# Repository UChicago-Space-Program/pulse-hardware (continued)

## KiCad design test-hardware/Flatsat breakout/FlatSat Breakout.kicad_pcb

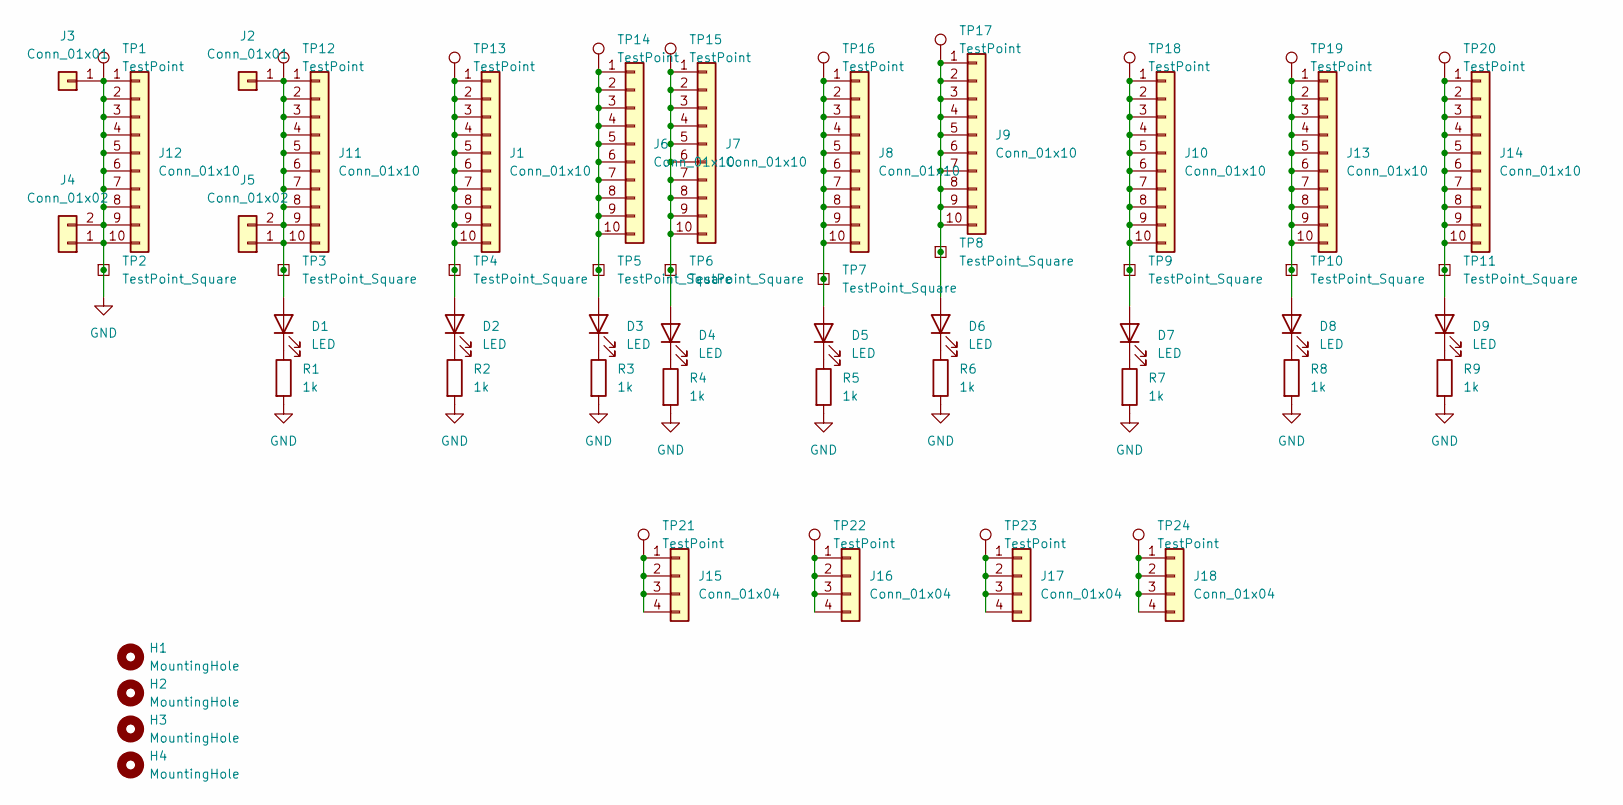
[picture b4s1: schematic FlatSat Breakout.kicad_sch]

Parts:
D1, D2, D3, D4, D5, D6, D7, D8, D9: LED; LED_0603_1608Metric
H1, H2, H3, H4: MountingHole; MountingHole_3.2mm_M3
J1, J6, J7, J8, J9, J10, J11, J12, J13, J14: Conn_01x10; PinHeader_1x10_P2.54mm_Vertical
J2, J3: Conn_01x01; Banana_Jack_1Pin
J4, J5: Conn_01x02; TerminalBlock_4Ucon_1x02_P3.50mm_Horizontal
J15, J16, J17, J18: Conn_01x04; PinHeader_1x04_P2.54mm_Vertical
R1, R2, R3, R4, R5, R6, R7, R8, R9: 1k; R_0603_1608Metric
TP1, TP12, TP13, TP14, TP15, TP16, TP17, TP18, TP19, TP20, TP21, TP22, TP23, TP24: TestPoint; TestPoint_Keystone_5000-5004_Miniature
TP2, TP3, TP4, TP5, TP6, TP7, TP8, TP9, TP10, TP11: TestPoint_Square; TestPoint_Pad_2.0x2.0mm

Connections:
GND: J3.1 (Pin_1_1), J4.1, J4.2, J12.1, J12.2, J12.3, J12.4, J12.5, J12.6, J12.7, J12.8, J12.9, J12.10, R1.2, R2.2, R3.2, R4.2, R5.2, R6.2, R7.2, R8.2, R9.2, TP1.1 (1_1), TP2.1 (1_1)
unnamed: D1.2 (A), J2.1 (Pin_1_1), J5.1, J5.2, J11.1, J11.2, J11.3, J11.4, J11.5, J11.6, J11.7, J11.8, J11.9, J11.10, TP3.1 (1_1), TP12.1 (1_1)
unnamed: D1.1 (K), R1.1
unnamed: D2.2 (A), J1.1, J1.2, J1.3, J1.4, J1.5, J1.6, J1.7, J1.8, J1.9, J1.10, TP4.1 (1_1), TP13.1 (1_1)
unnamed: D2.1 (K), R2.1
unnamed: D3.2 (A), J6.1, J6.2, J6.3, J6.4, J6.5, J6.6, J6.7, J6.8, J6.9, J6.10, TP5.1 (1_1), TP14.1 (1_1)
unnamed: D3.1 (K), R3.1
unnamed: D4.2 (A), J7.1, J7.2, J7.3, J7.4, J7.5, J7.6, J7.7, J7.8, J7.9, J7.10, TP6.1 (1_1), TP15.1 (1_1)
unnamed: D4.1 (K), R4.1
unnamed: D5.2 (A), J8.1, J8.2, J8.3, J8.4, J8.5, J8.6, J8.7, J8.8, J8.9, J8.10, TP7.1 (1_1), TP16.1 (1_1)
unnamed: D5.1 (K), R5.1
unnamed: D6.2 (A), J9.1, J9.2, J9.3, J9.4, J9.5, J9.6, J9.7, J9.8, J9.9, J9.10, TP8.1 (1_1), TP17.1 (1_1)
unnamed: D6.1 (K), R6.1
unnamed: D7.2 (A), J10.1, J10.2, J10.3, J10.4, J10.5, J10.6, J10.7, J10.8, J10.9, J10.10, TP9.1 (1_1), TP18.1 (1_1)
unnamed: D7.1 (K), R7.1
unnamed: D8.2 (A), J13.1, J13.2, J13.3, J13.4, J13.5, J13.6, J13.7, J13.8, J13.9, J13.10, TP10.1 (1_1), TP19.1 (1_1)
unnamed: D8.1 (K), R8.1
unnamed: D9.2 (A), J14.1, J14.2, J14.3, J14.4, J14.5, J14.6, J14.7, J14.8, J14.9, J14.10, TP11.1 (1_1), TP20.1 (1_1)
unnamed: D9.1 (K), R9.1
unnamed: J15.1, J15.2, J15.3, J15.4, TP21.1 (1_1)
unnamed: J16.1, J16.2, J16.3, J16.4, TP22.1 (1_1)
unnamed: J17.1, J17.2, J17.3, J17.4, TP23.1 (1_1)
unnamed: J18.1, J18.2, J18.3, J18.4, TP24.1 (1_1)

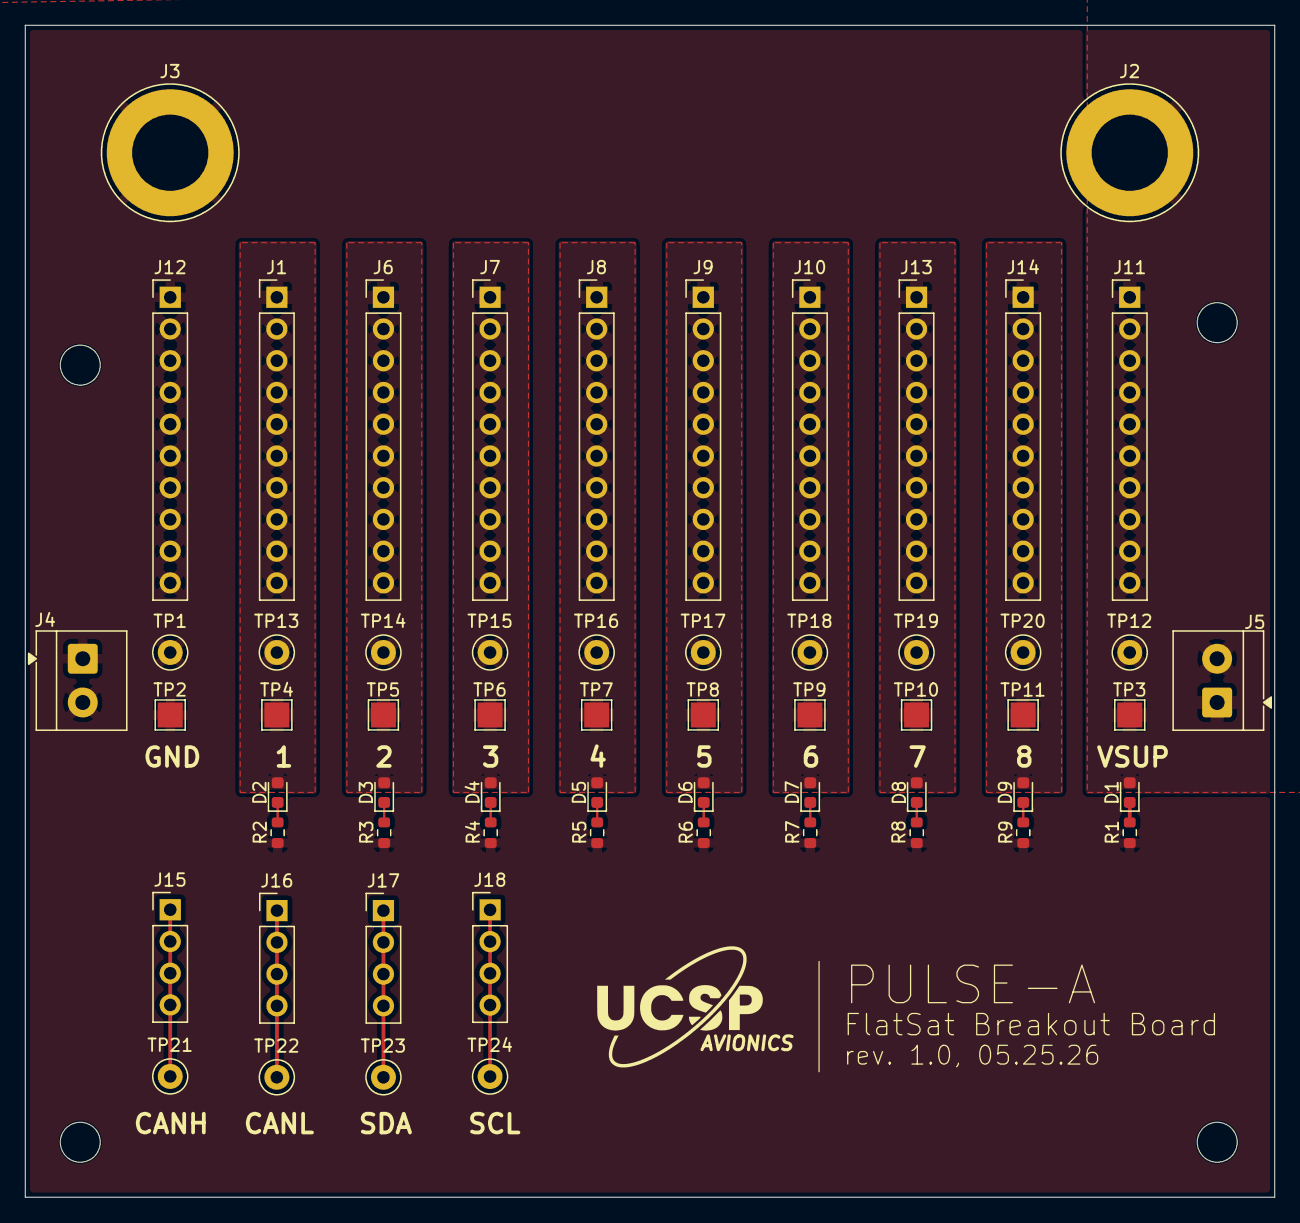
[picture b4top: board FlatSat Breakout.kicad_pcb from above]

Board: 2 copper layers, 100.0 x 93.8 mm, 64 parts (0 on the bottom side), 23 nets.

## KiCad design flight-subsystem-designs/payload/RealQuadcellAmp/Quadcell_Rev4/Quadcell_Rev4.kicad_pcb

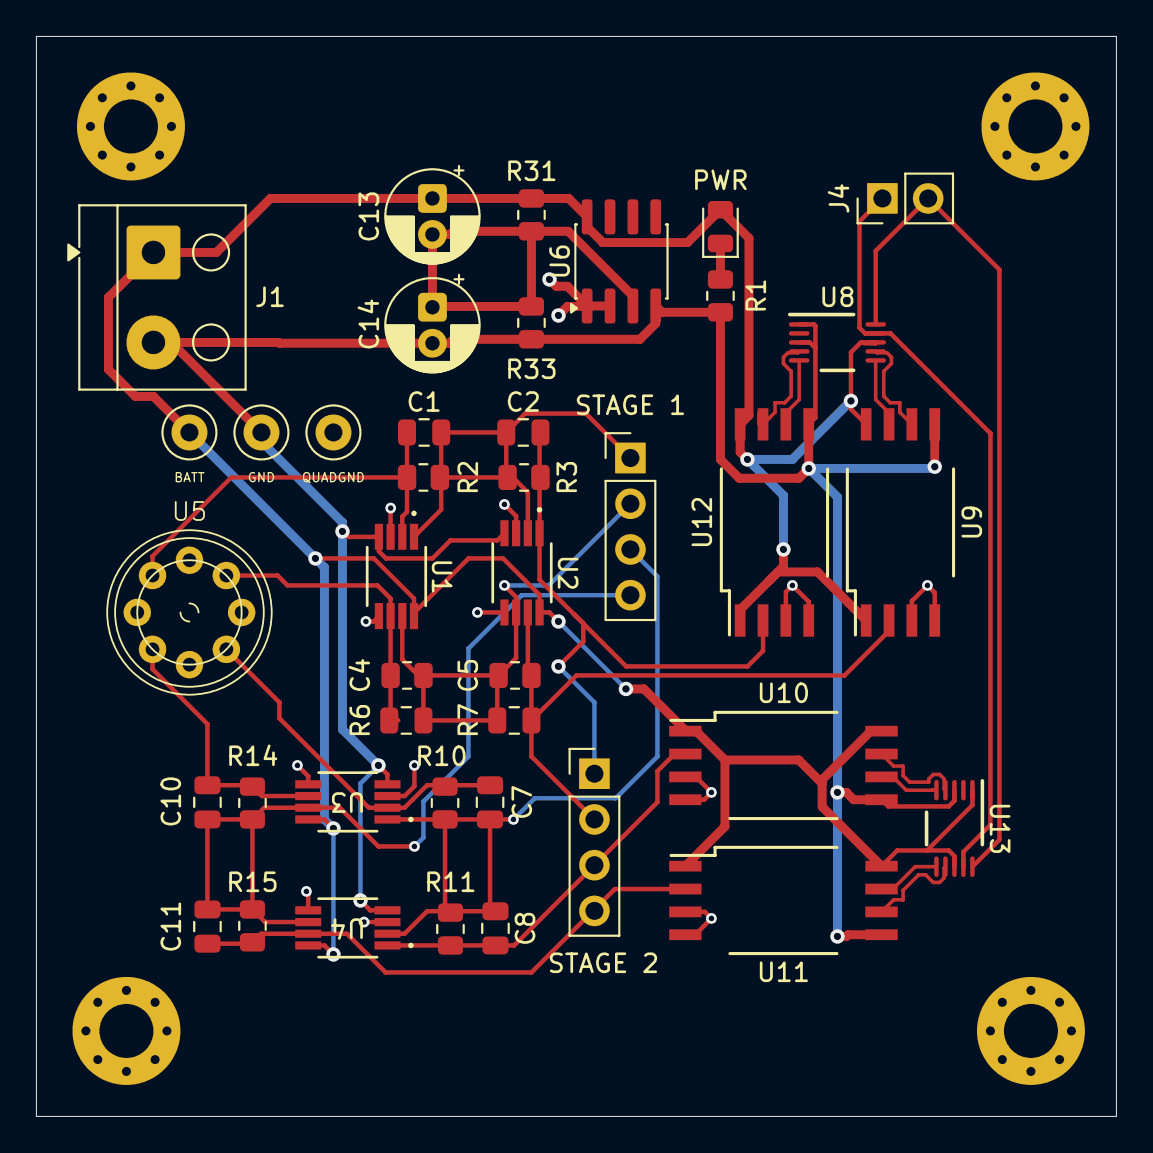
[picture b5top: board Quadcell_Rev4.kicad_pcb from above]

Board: 2 copper layers, 60.0 x 60.0 mm, 45 parts (0 on the bottom side), 27 nets.

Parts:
BATT: TestPoint; TestPoint_Loop_D2.50mm_Drill1.0mm
C1, C4, C7, C10: 5 pf; C_0805_2012Metric
C2, C5, C8, C11: 3 pf; C_0805_2012Metric
C13, C14: 220µF; CP_Radial_D5.0mm_P2.00mm
GND: TestPoint; TestPoint_Loop_D2.50mm_Drill1.0mm
H1, H2, H3, H4: MountingHole_Pad; MountingHole_3mm_Pad_Via
J1: Screw_Terminal_01x02; Altech_AK100_1x02_P5.00mm
J4: Conn_01x02_Pin; PinHeader_1x02_P2.54mm_Vertical
PWR: LED; D_0805_2012Metric
QUADGND: TestPoint; TestPoint_Loop_D2.50mm_Drill1.0mm
R1: 150; R_0805_2012Metric
R2, R6, R10, R14: 1 MΩ; R_0805_2012Metric
R3, R7, R11, R15: 15 MΩ; R_0805_2012Metric
R31, R33: 4.7k; R_0805_2012Metric
STAGE 1, STAGE 2: Conn_01x04_Pin; PinHeader_1x04_P2.54mm_Vertical
U1, U2, U3, U4: OPA2192IDR; OPA2192
U5: InGaAS-Q1000
U6: LM2904; SOIC-8_3.9x4.9mm_P1.27mm
U8, U13: ADS1115IDGST; ADS1115
U9, U10, U11, U12: AMC1301DWVR; AMC1301

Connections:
/digital_conversion/ADC1_N: U8.5 (AIN1), U12.6 (VOUTN)
/digital_conversion/ADC1_P: U8.4 (AIN0), U12.7 (VOUTP)
/digital_conversion/ADC2_N: U8.7 (AIN3), U9.6 (VOUTN)
/digital_conversion/ADC2_P: U8.6 (AIN2), U9.7 (VOUTP)
/digital_conversion/ADC3_N: U10.6 (VOUTN), U13.5 (AIN1)
/digital_conversion/ADC3_P: U10.7 (VOUTP), U13.4 (AIN0)
/digital_conversion/ADC4_N: U11.6 (VOUTN), U13.7 (AIN3)
/digital_conversion/ADC4_P: U11.7 (VOUTP), U13.6 (AIN2)
GND: C14.2, GND.1 (1_1), J1.2, R1.2, R33.2, U1.4 (V-), U2.4 (V-), U3.4 (V-), U4.4 (V-), U6.4 (V-), U8.1 (ADDR), U8.3 (GND), U9.5 (GND2), U10.5 (GND2), U11.5 (GND2), U12.5 (GND2), U13.3 (GND)
I2C_SCL: J4.2, U8.10 (SCL), U13.10 (SCL)
I2C_SDA: J4.1, U8.9 (SDA), U13.9 (SDA)
IN1: C1.1, R2.1, U1.2 (IN-), U5.1 (ANODE_1)
IN2: C4.1, R6.2, U1.6 (IN-), U5.2 (ANODE_2)
IN3: C7.1, R10.2, U3.2 (IN-), U5.3 (ANODE_3)
IN4: C10.1, R14.1, U3.6 (IN-), U5.4 (ANODE_4)
unnamed: PWR.1 (K), R1.1
unnamed: C13.2, C14.1, R31.2, R33.1, U6.3 (+)
QUAD_GND: H1.1 (1_1), H2.1 (1_1), H3.1 (1_1), H4.1 (1_1), QUADGND.1 (1_1), U1.3 (IN+), U1.5 (IN+), U2.3 (IN+), U2.5 (IN+), U3.3 (IN+), U3.5 (IN+), U4.3 (IN+), U4.5 (IN+), U5.0 (CAT), U6.1, U6.2 (-), U9.3 (VINN), U9.4 (GND1), U10.3 (VINN), U10.4 (GND1), U11.3 (VINN), U11.4 (GND1), U12.3 (VINN), U12.4 (GND1)
STAGE1_OUT1: C1.2, C2.1, R2.2, R3.1, STAGE 1.1, U1.1 (OUT), U2.2 (IN-)
STAGE1_OUT2: C4.2, C5.1, R6.1, R7.2, STAGE 1.2, U1.7 (OUT), U2.6 (IN-)
STAGE1_OUT3: C7.2, C8.1, R10.1, R11.2, STAGE 1.3, U3.1 (OUT), U4.2 (IN-)
STAGE1_OUT4: C10.2, C11.1, R14.2, R15.1, STAGE 1.4, U3.7 (OUT), U4.6 (IN-)
STAGE2_OUT1: C2.2, R3.2, STAGE 2.1, U2.1 (OUT), U12.2 (VINP)
STAGE2_OUT2: C5.2, R7.1, STAGE 2.2, U2.7 (OUT), U9.2 (VINP)
STAGE2_OUT3: C8.2, R11.1, STAGE 2.3, U4.1 (OUT), U10.2 (VINP)
STAGE2_OUT4: C11.2, R15.2, STAGE 2.4, U4.7 (OUT), U11.2 (VINP)
VCC: BATT.1 (1_1), C13.1, J1.1, PWR.2 (A), R31.1, U1.8 (V+), U2.8 (V+), U3.8 (V+), U4.8 (V+), U6.8 (V+), U8.8 (VDD), U9.1 (VDD1), U9.8 (VDD2), U10.1 (VDD1), U10.8 (VDD2), U11.1 (VDD1), U11.8 (VDD2), U12.1 (VDD1), U12.8 (VDD2), U13.1 (ADDR), U13.8 (VDD)

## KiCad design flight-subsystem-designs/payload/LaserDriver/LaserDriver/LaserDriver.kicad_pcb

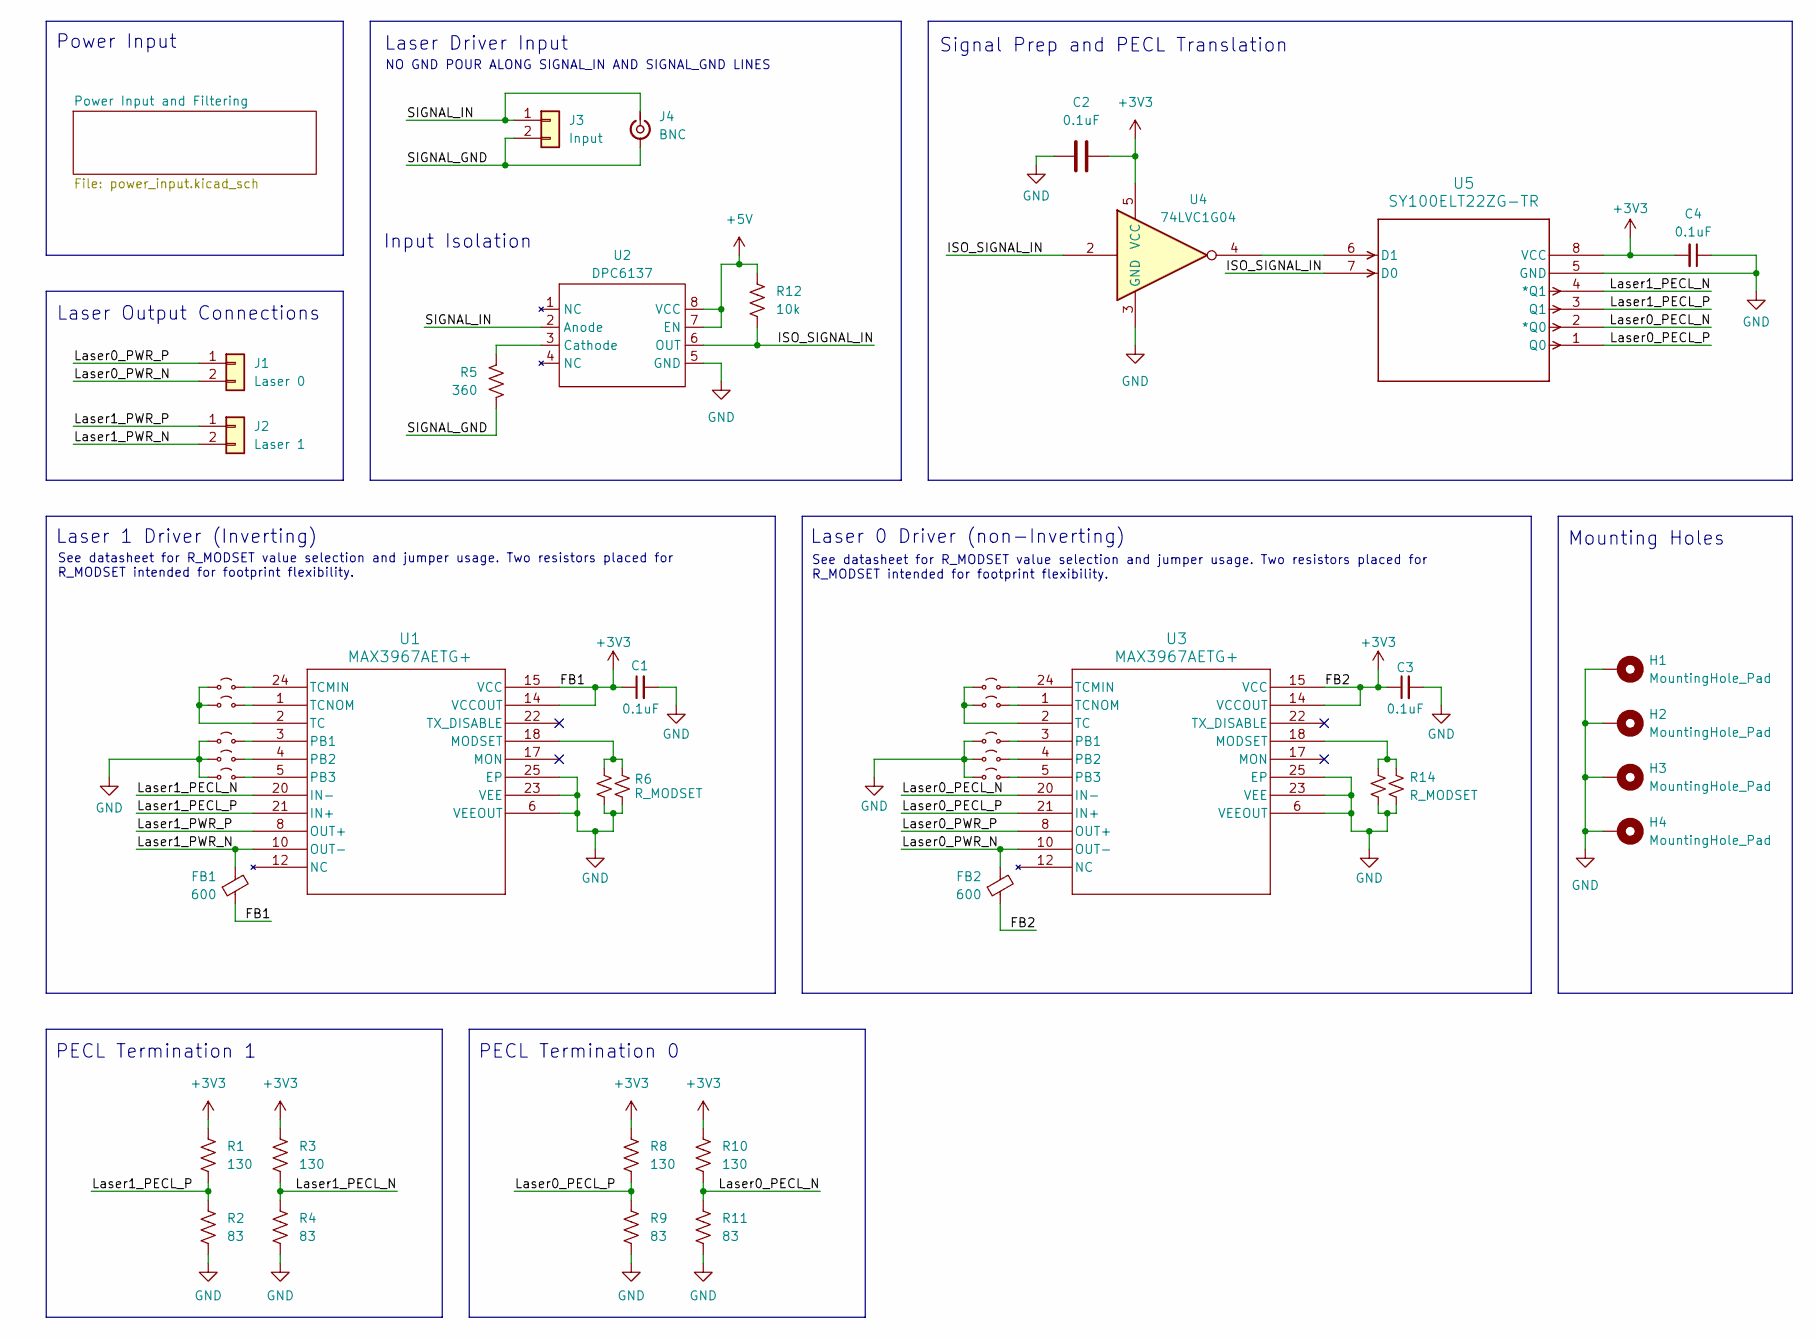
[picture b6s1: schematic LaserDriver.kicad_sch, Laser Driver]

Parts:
C1, C2, C3, C4: 0.1uF; C_0805_2012Metric_Pad1.18x1.45mm_HandSolder
FB1, FB2: 600; L_0805_2012Metric_Pad1.05x1.20mm_HandSolder; DigiKeyPN 445-MPZ2012S601AT000CT-ND
H1, H2, H3, H4: MountingHole_Pad; MountingHole_6.5mm_Pad
J1: Laser 0; PinHeader_1x02_P2.54mm_Vertical
J2: Laser 1; PinHeader_1x02_P2.54mm_Vertical
J3: Input; PinHeader_1x02_P2.54mm_Vertical
J4: BNC; BNC_TEConnectivity_1478204_Vertical
JP1, JP2, JP3, JP4, JP5, JP6, JP7, JP8, JP9, JP10: Jumper_2_Small_Open; SolderJumper-2_P1.3mm_Open_TrianglePad1.0x1.5mm
R1, R3, R8, R10: 130; R_0805_2012Metric_Pad1.20x1.40mm_HandSolder
R2, R4, R9, R11: 83; R_0805_2012Metric_Pad1.20x1.40mm_HandSolder
R5: 360; R_0805_2012Metric
R6, R14: R_MODSET; R_0805_2012Metric_Pad1.20x1.40mm_HandSolder
R7, R13: R_MODSET; R_Axial_DIN0204_L3.6mm_D1.6mm_P7.62mm_Horizontal
R12: 10k; R_0805_2012Metric
U1, U3: MAX3967AETG+; 21-0139_T2444&plus_4_MXM
U2: DPC6137; DIP-8_W10.16mm_LongPads; DigiKey 31-DPC6137W-TU-ND
U4: 74LVC1G04; SOT-23-5_HandSoldering; DigiKeyPN 296-11599-1-ND
U5: SY100ELT22ZG-TR; SOIC-8_M_MCH

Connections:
+3V3: C1.1, C2.2, C3.1, C4.2, FB1.1, FB2.1, R1.1, R3.1, R8.1, R10.1, U1.13 (VCCOUT), U1.14 (VCCOUT), U1.15 (VCC), U1.19 (VCC), U3.13 (VCCOUT), U3.14 (VCCOUT), U3.15 (VCC), U3.19 (VCC), U4.5 (VCC), U5.8 (VCC); also elsewhere on the board
+5V: R12.2, U2.7 (EN), U2.8 (VCC); also elsewhere on the board
/ISO_SIGNAL_IN: R12.1, U2.6 (OUT), U4.2, U5.7 (D0)
/Laser0_PECL_N: R10.2, R11.1, U3.20 (IN-), U5.2 (*Q0)
/Laser0_PECL_P: R8.2, R9.1, U3.21 (IN+), U5.1 (Q0)
/Laser0_PWR_N: FB2.2, J1.2, U3.10 (OUT-), U3.11 (OUT-)
/Laser0_PWR_P: J1.1, U3.8 (OUT+), U3.9 (OUT+)
/Laser1_PECL_N: R3.2, R4.1, U1.20 (IN-), U5.4 (*Q1)
/Laser1_PECL_P: R1.2, R2.1, U1.21 (IN+), U5.3 (Q1)
/Laser1_PWR_N: FB1.2, J2.2, U1.10 (OUT-), U1.11 (OUT-)
/Laser1_PWR_P: J2.1, U1.8 (OUT+), U1.9 (OUT+)
/SIGNAL_GND: J3.2, J4.2 (Ext), R5.1
/SIGNAL_IN: J3.1, J4.1 (In), U2.2 (Anode)
GND: C1.2, C2.1, C3.2, C4.1, H1.1 (1_1), H2.1 (1_1), H3.1 (1_1), H4.1 (1_1), JP3.1 (A), JP4.1 (A), JP5.1 (A), JP8.1 (A), JP9.1 (A), JP10.1 (A), R2.2, R4.2, R6.2, R7.2, R9.2, R11.2, R13.1, R14.1, U1.6 (VEEOUT), U1.7 (VEEOUT), U1.23 (VEE), U1.25 (EP), U2.5 (GND), U3.6 (VEEOUT), U3.7 (VEEOUT), U3.23 (VEE), U3.25 (EP), U4.3 (GND), U5.5 (GND); also elsewhere on the board
unnamed: JP1.1 (A), JP2.1 (A), U1.2 (TC)
unnamed: JP1.2 (B), U1.24 (TCMIN)
unnamed: JP2.2 (B), U1.1 (TCNOM)
unnamed: JP3.2 (B), U1.3 (PB1)
unnamed: JP4.2 (B), U1.4 (PB2)
unnamed: JP5.2 (B), U1.5 (PB3)
unnamed: JP6.1 (A), JP7.1 (A), U3.2 (TC)
unnamed: JP6.2 (B), U3.24 (TCMIN)
unnamed: JP7.2 (B), U3.1 (TCNOM)
unnamed: JP8.2 (B), U3.3 (PB1)
unnamed: JP9.2 (B), U3.4 (PB2)
unnamed: JP10.2 (B), U3.5 (PB3)
unnamed: R6.1, R7.1, U1.18 (MODSET)
unnamed: R5.2, U2.3 (Cathode)
unnamed: R13.2, R14.2, U3.18 (MODSET)
unnamed: U4.4, U5.6 (D1)

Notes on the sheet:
Laser Output Connections
Mounting Holes
NO GND POUR ALONG SIGNAL_IN AND SIGNAL_GND LINES
See datasheet for R_MODSET value selection and jumper usage. Two resistors placed for R_MODSET intended for footprint flexibility.
Laser 1 Driver (Inverting)
Laser Driver Input
PECL Termination 1
PECL Termination 0
Input Isolation
Signal Prep and PECL Translation
Laser 0 Driver (non-Inverting)
Power Input

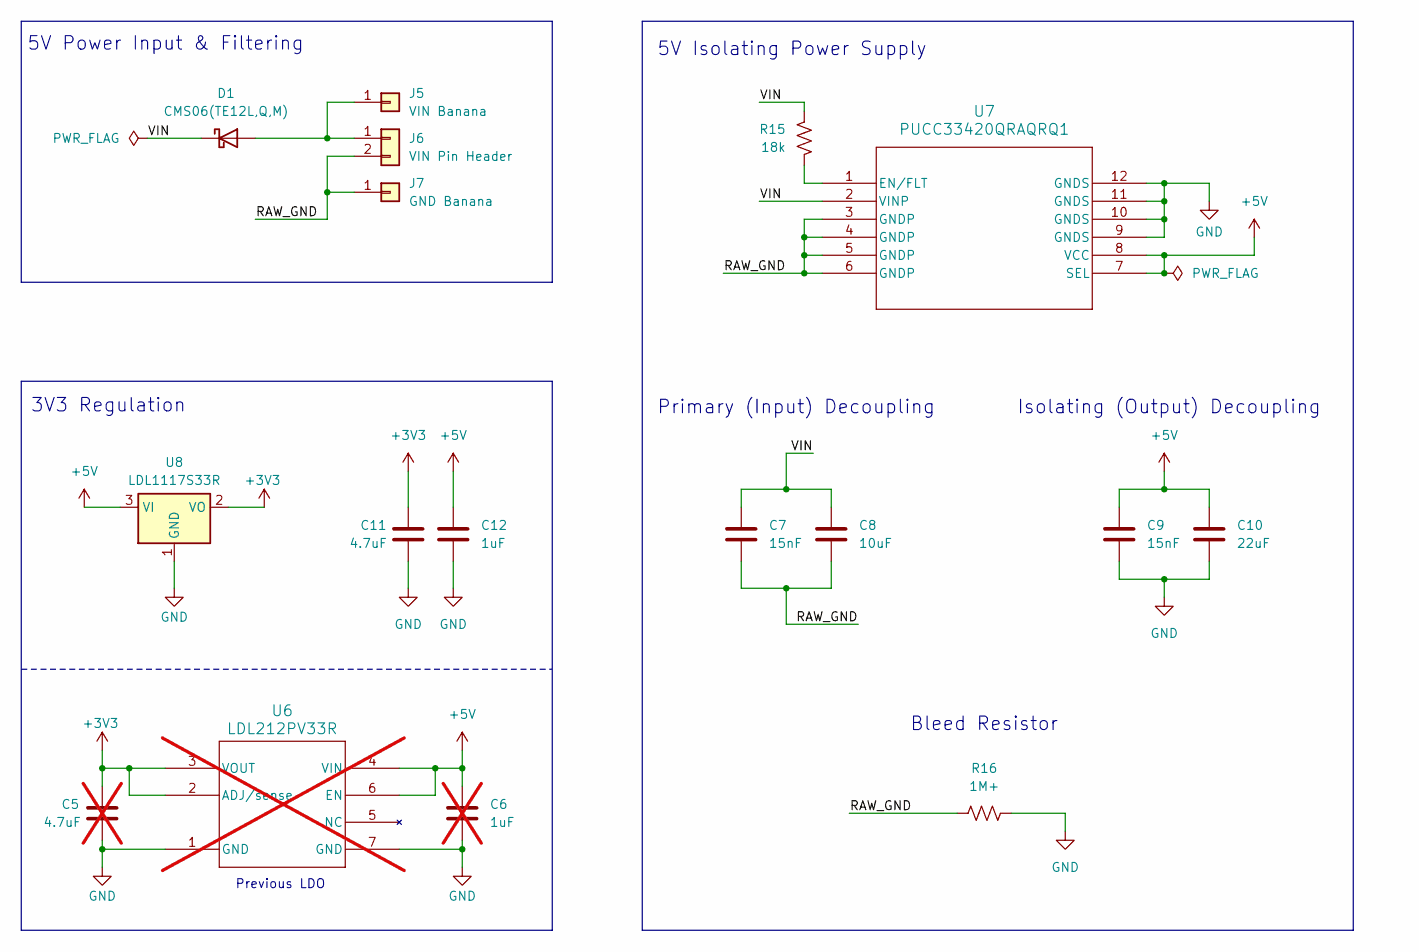
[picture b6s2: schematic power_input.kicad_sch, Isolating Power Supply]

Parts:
C5: 4.7uF; C_0805_2012Metric_Pad1.18x1.45mm_HandSolder; not fitted
C6: 1uF; C_0805_2012Metric_Pad1.18x1.45mm_HandSolder; not fitted
C7, C9: 15nF; C_0402_1005Metric
C8: 10uF; C_0805_2012Metric
C10: 22uF; C_0805_2012Metric
C11: 4.7uF; C_0805_2012Metric_Pad1.18x1.45mm_HandSolder
C12: 1uF; C_0805_2012Metric_Pad1.18x1.45mm_HandSolder
D1: CMS06(TE12L,Q,M); D_SOD-128; DigiKeyPN CMS06QMCT-ND
J5: VIN Banana; Banana_Jack_1Pin
J6: VIN Pin Header; PinHeader_1x02_P2.54mm_Vertical
J7: GND Banana; Banana_Jack_1Pin
R15: 18k; R_0805_2012Metric
R16: 1M+; R_0805_2012Metric_Pad1.20x1.40mm_HandSolder
U6: LDL212PV33R; DFN_V33R_STM; not fitted
U7: PUCC33420QRAQRQ1; VSON-FCRLF12_RAQ_TEX
U8: LDL1117S33R; SOT-223-3_TabPin2

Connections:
+3V3: C5.1, C11.1, U6.2 (ADJ/sense), U6.3 (VOUT), U8.2 (VO); also elsewhere on the board
+5V: C6.1, C9.1, C10.1, C12.1, U6.4 (VIN), U6.6 (EN), U7.7 (SEL), U7.8 (VCC), U8.3 (VI); also elsewhere on the board
/Power Input and Filtering/RAW_GND: C7.2, C8.2, J6.2, J7.1 (Pin_1_1), R16.1, U7.3 (GNDP), U7.4 (GNDP), U7.5 (GNDP), U7.6 (GNDP)
/Power Input and Filtering/VIN: C7.1, C8.1, D1.1 (K), R15.1, U7.2 (VINP)
GND: C5.2, C6.2, C9.2, C10.2, C11.2, C12.2, R16.2, U6.1 (GND), U6.7 (GND), U7.9 (GNDS), U7.10 (GNDS), U7.11 (GNDS), U7.12 (GNDS), U8.1 (GND); also elsewhere on the board
unnamed: D1.2 (A), J5.1 (Pin_1_1), J6.1
unnamed: R15.2, U7.1 (EN/FLT)

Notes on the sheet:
Isolating (Output) Decoupling
Previous LDO
Bleed Resistor
3V3 Regulation
5V Isolating Power Supply
Primary (Input) Decoupling
5V Power Input & Filtering

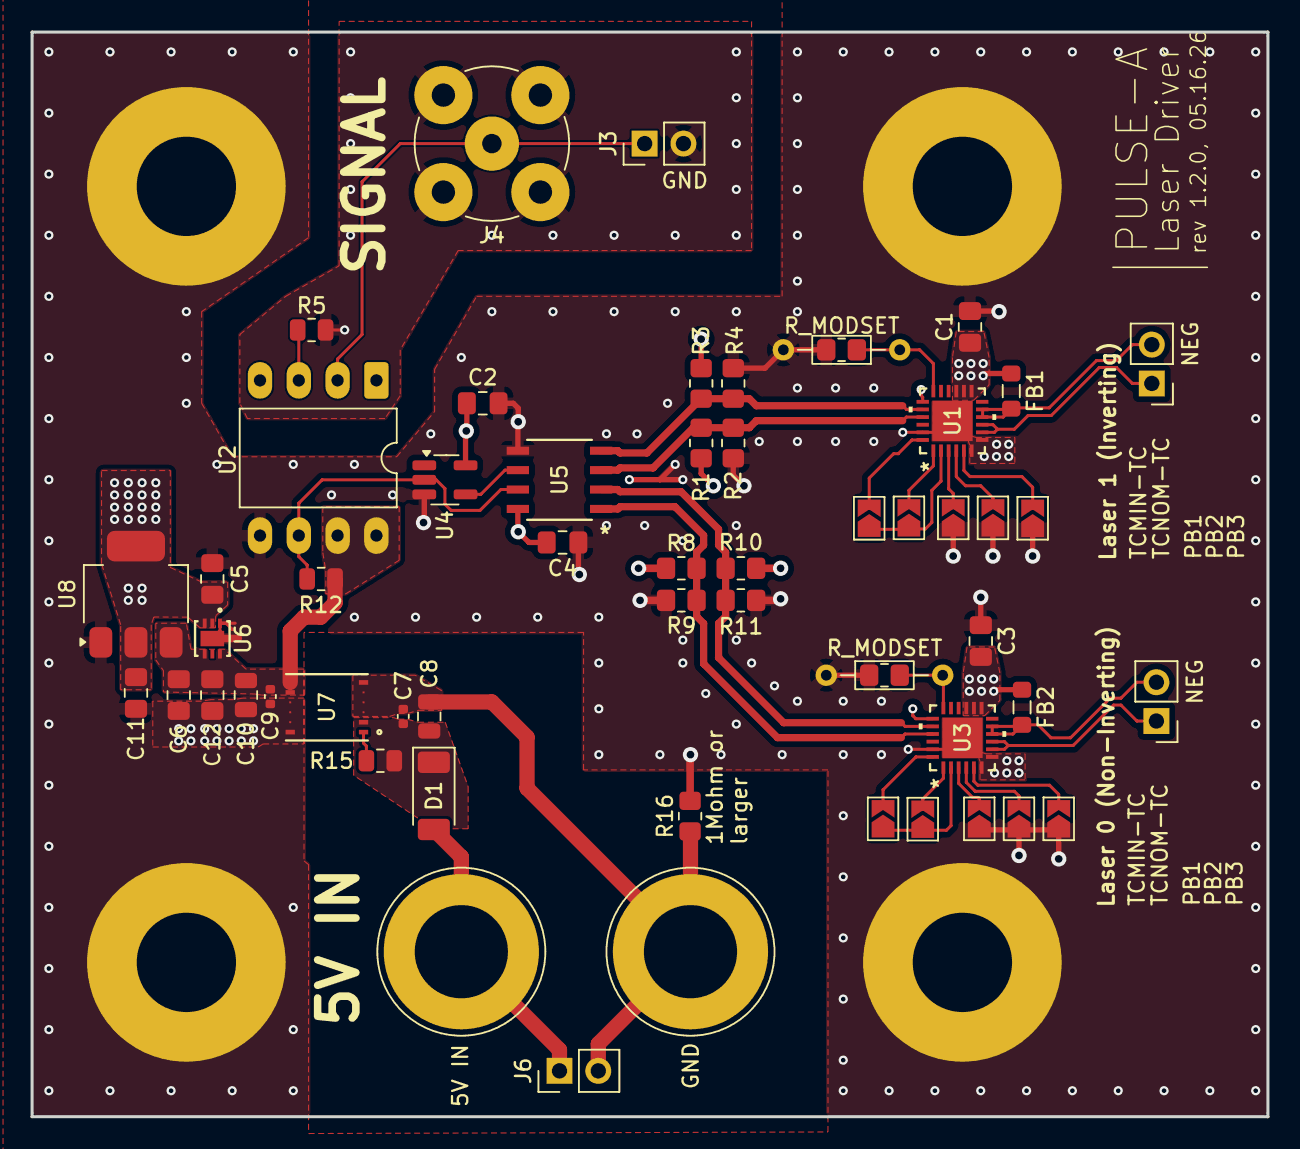
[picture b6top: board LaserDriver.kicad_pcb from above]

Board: 4 copper layers, 80.9 x 71.0 mm, 60 parts (0 on the bottom side), 34 nets.
